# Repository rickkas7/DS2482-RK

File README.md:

# DS2482 Library

The DS2482 is an I2C to 1-wire interface chip. It comes in two versions, the DS2482-100 (1-port) and DS2482-800 (8-port). Using an interface chip is helpful because most DS18B20/1-wire libraries use timing sensitive code and may run for extended periods with interrupts disabled. This can cause the rest of your program to have poor performance. 

The library fully supports both single-drop and multi-drop modes, allowing many DS18B20 sensors on a single 1-wire bus.

The DS2482 library is completely asynchronous, never blocking for more than the time to do an I2C read or write. Interrupts are never disabled.

Every call uses a C++11 lambda completion handler. The second part of this document has a bit of explanation of why and how it works.

The DS2482 also has an internal transistor to pull the 1-wire bus high during temperature conversion and flash writes. This allows the use of parasitic power mode, requiring only two wires for sensors (DQ and GND), with no separate power line. The library supports this as well.

The full API documentation can be browsed at [http://rickkas7.github.io/DS2482-RK/](http://rickkas7.github.io/DS2482-RK/). The same HTML documentation is in the docs folder in Github.

The official Github is: [https://github.com/rickkas7/DS2482-RK](https://github.com/rickkas7/DS2482-RK).

It's in the Particle community libraries as DS2482-RK.

## Common tasks

### Get temperature of one sensor (single-drop)

The code is also in examples, in the 01-single-drop directory.

```
#include "DS2482.h"

SerialLogHandler logHandler;

DS2482 ds(Wire, 3);

const unsigned long CHECK_PERIOD = 30000;
unsigned long lastCheck = 5000 - CHECK_PERIOD;

void setup() {
	Serial.begin(9600);
	ds.setup();

	DS2482DeviceReset::run(ds,  {
		Serial.printlnf("deviceReset=%d", status);
	});

	Serial.println("setup complete");
}

void loop() {

	ds.loop();

	if (millis() - lastCheck >= CHECK_PERIOD) {
		lastCheck = millis();

		// For single-drop you can pass an empty address to get the temperature of the only
		// sensor on the 1-wire bus
		DS24821WireAddress addr;

		DS2482GetTemperatureCommand::run(ds, addr,  {
			if (status == DS2482Command::RESULT_DONE) {
				char buf[32];
				snprintf(buf, sizeof(buf), "%.4f", tempC);

				Serial.printlnf("temperature=%s deg C", buf);
				Particle.publish("temperature", buf, PRIVATE);
			}
			else {
				Serial.printlnf("DS2482GetTemperatureCommand failed status=%d", status);
			}
		});
	}
}
```

### Get temperatures of multiple sensors (multi-drop)

The code is also in examples, in the 02-multi-drop directory.

```
#include "DS2482.h"

SerialLogHandler logHandler;

DS2482 ds(Wire, 3);

DS2482DeviceListStatic<10> deviceList;
const unsigned long CHECK_PERIOD = 30000;
unsigned long lastCheck = 10000 - CHECK_PERIOD;

void setup() {
	Serial.begin(9600);
	ds.setup();

	DS2482DeviceReset::run(ds,  {
		Serial.printlnf("deviceReset=%d", status);
		DS2482SearchBusCommand::run(ds, deviceList,  {

			if (status != DS2482Command::RESULT_DONE) {
				Serial.printlnf("DS2482SearchBusCommand status=%d", status);
				return;
			}

			Serial.printlnf("Found %u devices", deviceList.getDeviceCount());
		});
	});

	Serial.println("setup complete");
}

void loop() {

	ds.loop();

	if (millis() - lastCheck >= CHECK_PERIOD) {
		lastCheck = millis();

		if (deviceList.getDeviceCount() > 0) {

			DS2482GetTemperatureForListCommand::run(ds, deviceList,  {
				if (status != DS2482Command::RESULT_DONE) {
					Serial.printlnf("DS2482GetTemperatureForListCommand status=%d", status);
					return;
				}

				Serial.printlnf("got temperatures!");

				for(size_t ii = 0; ii < deviceList.getDeviceCount(); ii++) {
					Serial.printlnf("%s valid=%d C=%f F=%f",
							deviceList.getAddressByIndex(ii).toString().c_str(),
							deviceList.getDeviceByIndex(ii).getValid(),
							deviceList.getDeviceByIndex(ii).getTemperatureC(),
							deviceList.getDeviceByIndex(ii).getTemperatureF());
				}

			});
		}
		else {
			Serial.printlnf("no devices found");
		}
	}
}
```

### Multi-drop with parasitic power

Just as the previous example, except within loop the call to D2482GetTemperatureListCommand::run has an extra optional fluent parameter, `.withParasiticPower()`.

```
			DS2482GetTemperatureForListCommand::run(ds, deviceList,  {
				if (status != DS2482Command::RESULT_DONE) {
					Serial.printlnf("DS2482GetTemperatureForListCommand status=%d", status);
					return;
				}

				Serial.printlnf("got temperatures!");

				for(size_t ii = 0; ii < deviceList.getDeviceCount(); ii++) {
					Serial.printlnf("%s valid=%d C=%f F=%f",
							deviceList.getAddressByIndex(ii).toString().c_str(),
							deviceList.getDeviceByIndex(ii).getValid(),
							deviceList.getDeviceByIndex(ii).getTemperatureC(),
							deviceList.getDeviceByIndex(ii).getTemperatureF());
				}

			}).withParasiticPower();
```

### Multi-drop with JSON publish

This example is like the previous, except it publishes multiple sensor values via a single Particle.publish in JSON format (up to 10 DS18B20s supported).

The full examples is only in github, in the test-projects/10-multidrop-json directory. This is because it requires another library, JsonParserGeneratorRK, in addition to DS2482-RK.

```
#include "DS2482.h"
#include "JsonParserGeneratorRK.h"

SerialLogHandler logHandler;

DS2482 ds(Wire, 3);

DS2482DeviceListStatic<10> deviceList;
JsonWriterStatic<256> jsonWriter;

const unsigned long CHECK_PERIOD = 30000;
unsigned long lastCheck = 10000 - CHECK_PERIOD;

void setup() {
	Serial.begin(9600);
	ds.setup();

	DS2482DeviceReset::run(ds,  {
		Serial.printlnf("deviceReset=%d", status);
		DS2482SearchBusCommand::run(ds, deviceList,  {

			if (status != DS2482Command::RESULT_DONE) {
				Serial.printlnf("DS2482SearchBusCommand status=%d", status);
				return;
			}

			Serial.printlnf("Found %u devices", deviceList.getDeviceCount());
		});
	});

	Serial.println("setup complete");
}

void loop() {

	ds.loop();

	if (millis() - lastCheck >= CHECK_PERIOD) {
		lastCheck = millis();

		if (deviceList.getDeviceCount() > 0) {

			DS2482GetTemperatureForListCommand::run(ds, deviceList,  {
				if (status != DS2482Command::RESULT_DONE) {
					Serial.printlnf("DS2482GetTemperatureForListCommand status=%d", status);
					return;
				}

				Serial.printlnf("got temperatures!");

				// Initialize the JsonWriter object and sets it to send 2 decimal places
				jsonWriter.init();
				jsonWriter.setFloatPlaces(2);

				// startObject is for the outer object and must be balanced with finishObjectOrArray.
				jsonWriter.startObject();

				// Write the actual temperatures
				for(size_t ii = 0; ii < deviceList.getDeviceCount(); ii++) {
					if (deviceList.getDeviceByIndex(ii).getValid()) {
						// This creates a key of the form "t0" for the first, "t1" for the second, ...
						char key[4];
						key[0] = 't';
						key[1] = '0' + ii;
						key[2] = 0;

						// Inserts the float as a key value pair
						jsonWriter.insertKeyValue(key, deviceList.getDeviceByIndex(ii).getTemperatureC());
					}
				}

				jsonWriter.finishObjectOrArray();

				Serial.println(jsonWriter.getBuffer());
				Particle.publish("temperature", jsonWriter.getBuffer(), PRIVATE);

				// Example output:
				// {"t0":23.56,"t1":23.12}
			});
		}
		else {
			Serial.printlnf("no devices found");
		}
	}
}
```

Example serial output:

```
got temperatures!
{"t0":23.56,"t1":23.12}
```

Because the 1-wire bus search is deterministic, it will always returns the sensors in the same order, sorted by 1-wire device address (increasing).

### Test Suite

There's a test suite for the library in Github, in test-projects/11-testboard. This is a hardware and software combination used to do regression testing on the library.

## About lambdas, fluent-style and more

The DS2482 library uses a C++11 style of coding that is very powerful, but will probably be foreign to you if you learned old-school C and C++. It's actually more like the way Javascript/node.js is programmed.

One of the main advantages of the DS2482 library is that it's completely asynchronous. No call blocks for more than the time it takes to make an I2C transfer. This is important because getting a temperature sensor reading can take 750 milliseconds, and most DS18B20 software libraries block during conversion.

### Synchronous way

Using the [DS18B20 library](https://build.particle.io/libs/DS18B20/0.1.7/tab/DS18B20.cpp), you make a call like this:

```
float tempC = ds.getTemperature(addr);
```

The main loop thread is blocked during this call for 750 milliseconds, which may affect performance elsewhere in your code. 

### State machines

One common way of implementing asynchronous code is state machines. This is a bit of pseudo-code of what a state machine version might look like. 

```
void loop() {
	switch(state) {
	case GET_TEMPERATURE_STATE:
		ds.startTemperature();
		state = TEMPERATURE_WAIT_STATE;
		break;

	case TEMPERATURE_WAIT_STATE:
		if (ds.isTemperatureDone()) {
			float temp = ds.readTemperature();
			state = ANOTHER_STATE;
		}
		break;
	}
}
```

State machines are really powerful, and actually how the DS2482 library is implemented internally, but can get a bit unwieldy.

### Callbacks

Callback functions are another common way of handling asynchronous code, like in this pseudo-code example:

```
void temperatureCallback(float temp) {
	Serial.printlnf("got temperature %f", temp);
}

void loop() {
	if (millis() - lastCheck >= CHECK_PERIOD) {
		lastCheck = millis();
		ds.getTemperature(temperatureCallback);
	}
}
```

The problem with callbacks is that it's a pain to pass state data to the callback, and it requires some effort to make a callback handler a class member function.

### The Lambda

The lambda solves some of the problems with callbacks. Here's an example of doing an asynchronous device reset call:

```
void setup() {
	Serial.begin(9600);
	ds.setup();

	DS2482DeviceReset::run(ds,  {
		Serial.printlnf("deviceReset=%d", status);
	});

	Serial.println("setup complete");
}
```

The syntax is a little weird, and I'll get to that a moment, however the important thing is that this block of code, the lambda, is executed later.

```
	 {
		Serial.printlnf("deviceReset=%d", status);
	}
```

The 

```
setup complete
```

message appears next.

When the asynchronous device reset completes, the block runs and

```
deviceReset=1
``` 

will likely be printed to the serial console. Note, however, that the lines after the block, like printing setup complete! won't happen a second time.

A declaration of a lambda function looks like 

```
 {
	// Code goes here
}
``` 

The `[]` part is the capture, which we'll discuss in a moment, and `(DS2482DeviceReset&, int status)` is a function parameter declaration. Basically the callback is a function that takes two parameters, a `DS2482DeviceReset&` object (not used here) and an `int status` (for status).

### Nesting calls

This example demonstrates two handy things:

- Making your lambda be a class member
- Nesting lambdas for sequential operations

```
void TestClass::check() {
	DS2482SearchBusCommand::run(ds, deviceList, [this](DS2482SearchBusCommand &obj, int status) {

		if (status != DS2482Command::RESULT_DONE) {
			Serial.printlnf("DS2482SearchBusCommand status=%d", status);
			return;
		}

		if (deviceList.getDeviceCount() == 0) {
			Serial.println("no devices");
			return;
		}

		DS2482GetTemperatureForListCommand::run(ds, obj.getDeviceList(), [this](DS2482GetTemperatureForListCommand&, int status, DS2482DeviceList &deviceList) {
			if (status != DS2482Command::RESULT_DONE) {
				Serial.printlnf("DS2482GetTemperatureForListCommand status=%d", status);
				return;
			}

			Serial.printlnf("got temperatures!");

			for(size_t ii = 0; ii < deviceList.getDeviceCount(); ii++) {
				Serial.printlnf("%s valid=%d C=%f F=%f",
						deviceList.getAddressByIndex(ii).toString().c_str(),
						deviceList.getDeviceByIndex(ii).getValid(),
						deviceList.getDeviceByIndex(ii).getTemperatureC(),
						deviceList.getDeviceByIndex(ii).getTemperatureF());
			}

		});
	});
}
```

You'll notice the slightly different syntax in the capture, the part in the square brackets:

```
DS2482SearchBusCommand::run(ds, deviceList, [this](DS2482SearchBusCommand &obj, int status) {
```

Instead of just being `[]` it's `[this]`. That means that `this`, your class instance, is captured, and available inside the lambda. It essentially makes the inner function a class member, available to access class member functions and variables.

You can capture multiple variables, separated by commas. You can capture function parameters and local variables, for example.

The other thing is that you can nest these, so each new indent in occurs at a later time. If you don't like that style, however, you can just split your code into separate member functions like this:

```
void TestClass::searchBus() {

	DS2482SearchBusCommand::run(ds, deviceList, [this](DS2482SearchBusCommand &obj, int status) {

		if (status != DS2482Command::RESULT_DONE) {
			Serial.printlnf("DS2482SearchBusCommand status=%d", status);
			return;
		}

		if (deviceList.getDeviceCount() == 0) {
			Serial.println("no devices");
			return;
		}

		getTemperatures();
	});
}

void TestClass::getTemperatures() {

	DS2482GetTemperatureForListCommand::run(ds, deviceList, [this](DS2482GetTemperatureForListCommand&, int status, DS2482DeviceList &deviceList) {
		if (status != DS2482Command::RESULT_DONE) {
			Serial.printlnf("DS2482GetTemperatureForListCommand status=%d", status);
			return;
		}

		Serial.printlnf("got temperatures!");

		for(size_t ii = 0; ii < deviceList.getDeviceCount(); ii++) {
			Serial.printlnf("%s valid=%d C=%f F=%f",
					deviceList.getAddressByIndex(ii).toString().c_str(),
					deviceList.getDeviceByIndex(ii).getValid(),
					deviceList.getDeviceByIndex(ii).getTemperatureC(),
					deviceList.getDeviceByIndex(ii).getTemperatureF());
		}
	});

}
```

### Optional parameters

Within the library, optional parameters are passed fluent-style instead of using C++ optional parameters. The fluent-style parameters are easier to identify and don't depend on order. For example:

```
DS2482GetTemperatureCommand::run(ds, addr, [this,completion](DS2482GetTemperatureCommand&, int status, float t) {
		if (status != DS2482Command::RESULT_DONE) {
			Log.error("FAILURE DS2482GetTemperatureCommand failed %d bus %s", status, name.c_str());
			completion();
			return;
		}

		testsComplete(completion);
	}).withParasiticPower(isParasiticPowered).withMaxRetries(1);
```

Of note:

- The optional parameters go after the `})` that closes the run command.
- You can chain as many or as few as you want in any order.
- The names all begin with `with`.

In this example, it uses parasitic power or not based on the member variable `isParasiticPowered` and limits the number of retries to 1.

### Run methods

All of the asynchronous functions are implemented as separate classes with a static run method. For example `DS2482GetTemperatureCommand::run`.

This is done because the objects need to be allocated on the heap (using new), not stack allocated. Since they continue after your function returns, stack allocated classes wouldn't work because they would go away when the enclosing function returns.

The run methods take care of allocated the objects and enqueueing them for execution so they make sure the objects gets deleted later, as well.

## Hardware examples

The hardware examples are in Github in the hardware directory. The Eagle board and schematic files are there as well.

### 1-port

This is a simple breakout board for the DS2482-100 (1-port):

### 8-port

This is a simple board for the DS2482-800 (8-port), though it's only populated for 6 ports. Four of them are modular jacks, designed to connect with one of the remote sensors below.

### DS18B20-regular

This is a simple DS18B20 remote sensor with a modular connector. The extra chip is a bridge rectifier, which makes it tolerant of having the connector polarity reversed, for example yellow and black reversed. This happens frequently when the flat cable is used and there isn't the proper twist in it.

### DS18B20-Mini

This is an even smaller DS18B20 remote sensor with a modular connector. It leaves off the screw terminal space and does not include the bridge rectifier, so make sure you don't cross the yellow and black wires!

### test-board

This is how I regression test the library. It's a board with DS2482-100 (1-port), DS2482-800 (8-port), 8x DS18B20s, and MCP23008 so I can switch the DS18B20s between powered and parasitic power mode individually.

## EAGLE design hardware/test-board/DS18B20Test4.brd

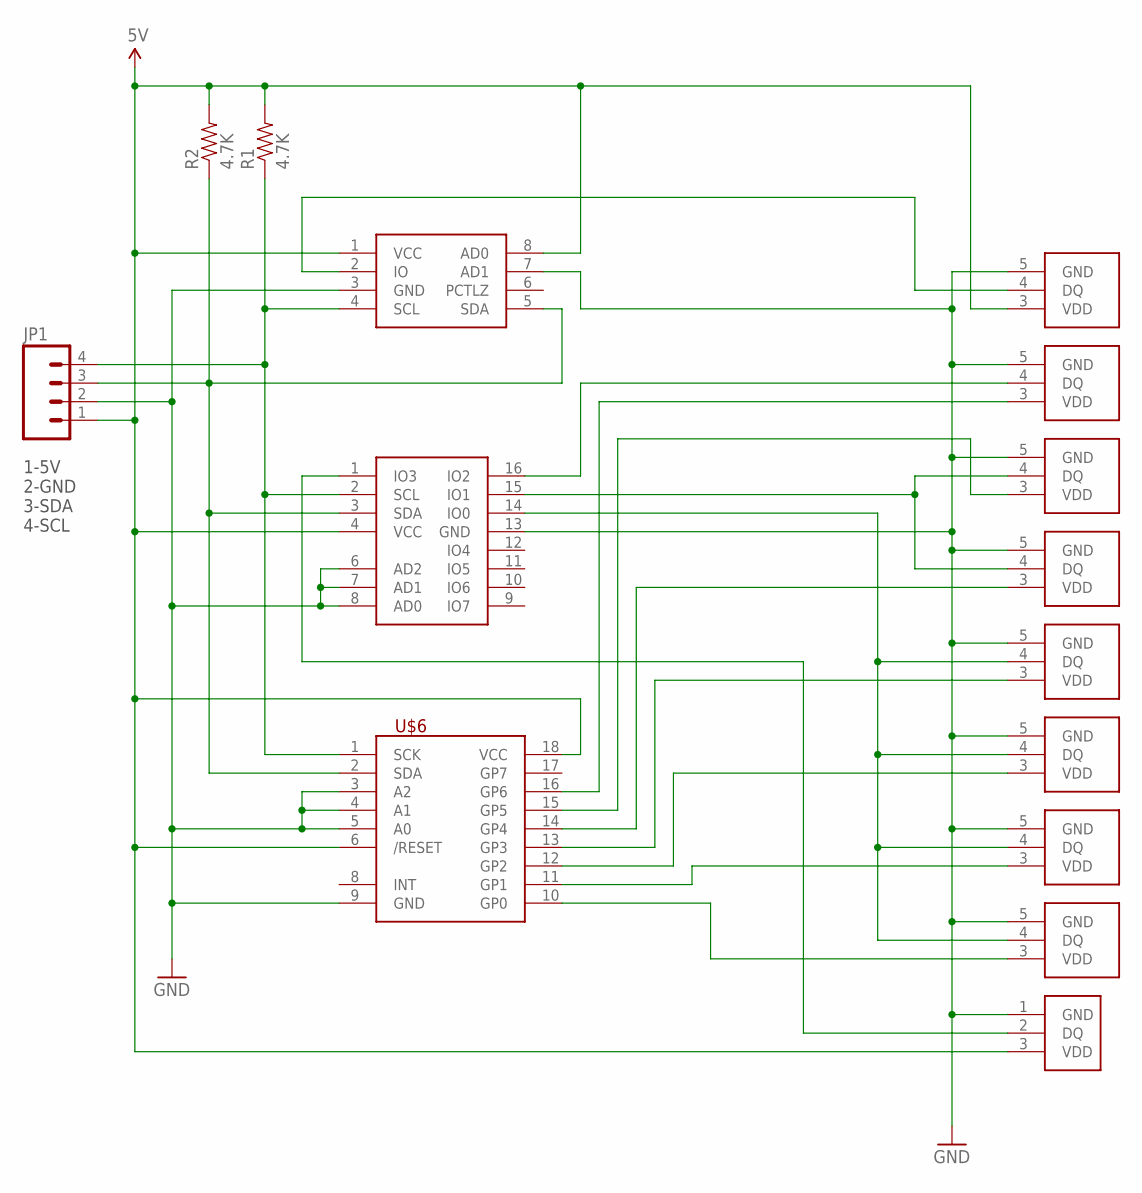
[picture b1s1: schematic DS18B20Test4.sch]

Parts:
JP1: M04PTH; 1X04
R1, R2: 4.7K; 0603-RES
U$1: DS2482-100; 8-SOIC-MAXIM
U$2: DS2482-800; 16-SOIC-MAXIM
U$3: TERMBLOCK-1WIRE
U$4, U$5, U$7, U$8, U$9, U$10, U$11, U$12: DS18B208-SOIC; DS18B20-S0
U$6: MCP23008; SOIC-18-W-MAXIM

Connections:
5V: JP1.1, R1.2, R2.2, U$1.1 (VCC), U$1.8 (AD0), U$2.4 (VCC), U$3.3 (VDD), U$4.3 (VDD), U$6.6 (/RESET), U$6.18 (VCC)
GND: JP1.2, U$1.3 (GND), U$1.7 (AD1), U$2.6 (AD2), U$2.7 (AD1), U$2.8 (AD0), U$2.13 (GND), U$3.1 (GND), U$4.5 (GND), U$5.5 (GND), U$6.3 (A2), U$6.4 (A1), U$6.5 (A0), U$6.9 (GND), U$7.5 (GND), U$8.5 (GND), U$9.5 (GND), U$10.5 (GND), U$11.5 (GND), U$12.5 (GND)
unnamed: U$1.2 (IO), U$4.4 (DQ)
unnamed: U$2.16 (IO2), U$5.4 (DQ)
unnamed: U$2.15 (IO1), U$7.4 (DQ), U$8.4 (DQ)
unnamed: U$2.14 (IO0), U$9.4 (DQ), U$10.4 (DQ), U$11.4 (DQ), U$12.4 (DQ)
unnamed: U$2.1 (IO3), U$3.2 (DQ)
unnamed: U$5.3 (VDD), U$6.16 (GP6)
unnamed: U$6.15 (GP5), U$7.3 (VDD)
unnamed: U$6.14 (GP4), U$8.3 (VDD)
unnamed: U$6.13 (GP3), U$9.3 (VDD)
unnamed: U$6.12 (GP2), U$10.3 (VDD)
unnamed: U$6.11 (GP1), U$11.3 (VDD)
unnamed: U$6.10 (GP0), U$12.3 (VDD)
SCL: JP1.4, R1.1, U$1.4 (SCL), U$2.2 (SCL), U$6.1 (SCK)
SDA: JP1.3, R2.1, U$1.5 (SDA), U$2.3 (SDA), U$6.2 (SDA)

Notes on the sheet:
1-5V 2-GND 3-SDA 4-SCL

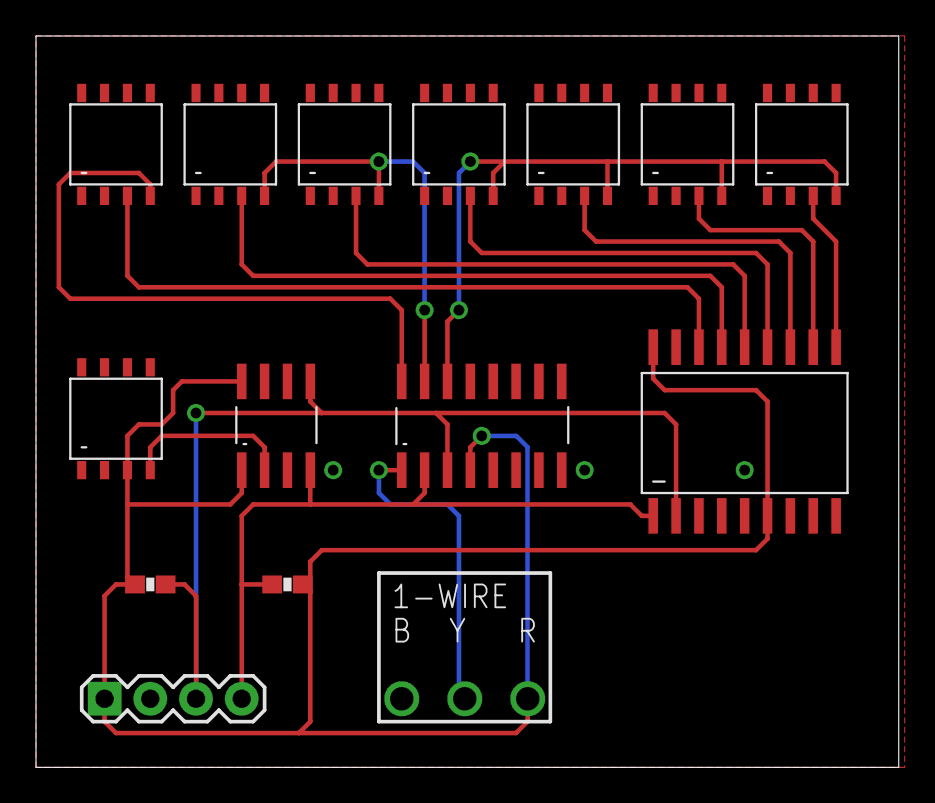
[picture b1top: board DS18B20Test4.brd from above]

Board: 2 copper layers, 47.9 x 40.6 mm, 15 parts (0 on the bottom side), 16 nets.

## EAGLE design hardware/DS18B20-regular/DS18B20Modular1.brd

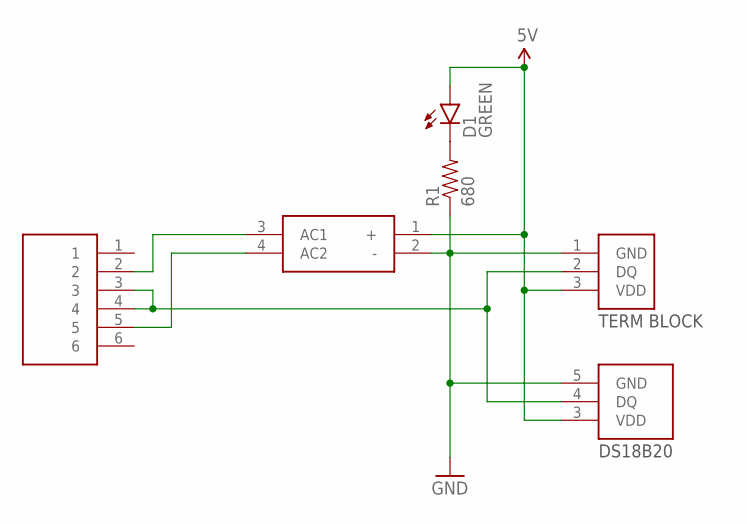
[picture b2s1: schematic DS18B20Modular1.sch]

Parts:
D1: GREEN; LED-0603
J1: MODULAR-JACK-6P6C-1
R1: 680; 0805
U$1: RECTIFIER-MB1S; 4-SOIC-FAIRCHILD
U$2: TERMBLOCK-1WIRE
U$3: DS18B208-SOIC; DS18B20-S0

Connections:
5V: D1.A, U$1.1 (+), U$2.3 (VDD), U$3.3 (VDD)
GND: R1.1, U$1.2 (-), U$2.1 (GND), U$3.5 (GND)
unnamed: J1.3, J1.4, U$2.2 (DQ), U$3.4 (DQ)
unnamed: J1.2, U$1.3 (AC1)
unnamed: J1.5, U$1.4 (AC2)
unnamed: D1.C, R1.2

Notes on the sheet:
DS18B20
TERM BLOCK

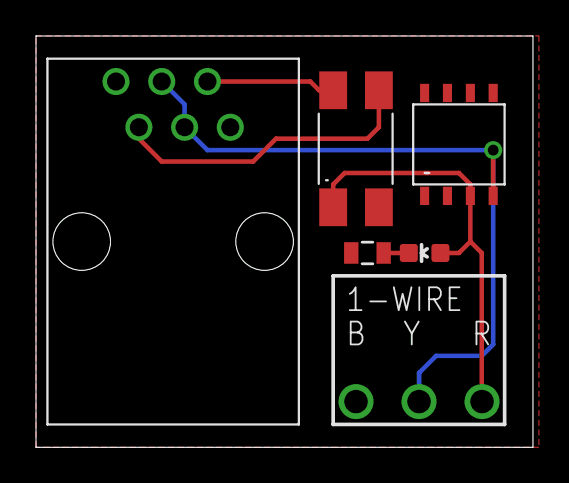
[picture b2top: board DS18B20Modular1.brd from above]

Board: 2 copper layers, 27.6 x 22.9 mm, 6 parts (0 on the bottom side), 6 nets.

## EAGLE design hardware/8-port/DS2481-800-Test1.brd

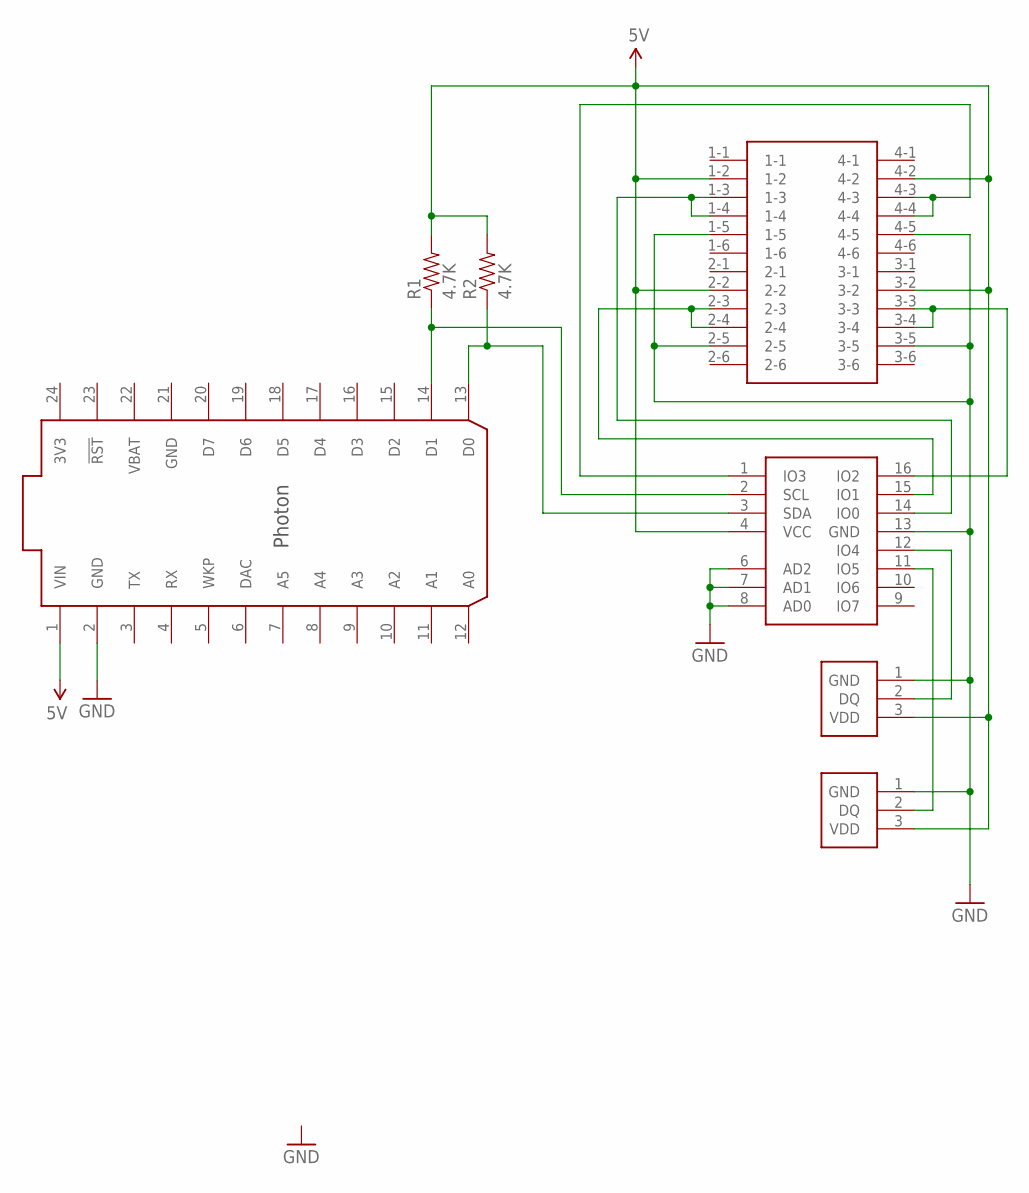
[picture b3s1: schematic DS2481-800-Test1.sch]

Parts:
R1, R2: 4.7K; 0603-RES
U$1: PHOTON_WITH_HEADERS; PHOTON
U$2: DS2482-800; 16-SOIC-MAXIM
U$3: MODULAR-JACK-6P6C-4
U$4, U$5: TERMBLOCK-1WIRE

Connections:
3V3: U$1.24 (3V3)
5V: R1.2, R2.2, U$1.1 (VIN), U$2.4 (VCC), U$3.1-2, U$3.2-2, U$3.3-2, U$3.4-2, U$4.3 (VDD), U$5.3 (VDD)
GND: U$1.2 (GND), U$1.21 (GND), U$2.6 (AD2), U$2.7 (AD1), U$2.8 (AD0), U$2.13 (GND), U$3.1-5, U$3.2-5, U$3.3-5, U$3.4-5, U$4.1 (GND), U$5.1 (GND)
unnamed: U$2.14 (IO0), U$3.1-3, U$3.1-4
unnamed: U$2.15 (IO1), U$3.2-3, U$3.2-4
unnamed: U$2.16 (IO2), U$3.3-3, U$3.3-4
unnamed: U$2.1 (IO3), U$3.4-3, U$3.4-4
unnamed: U$2.12 (IO4), U$4.2 (DQ)
unnamed: U$2.11 (IO5), U$5.2 (DQ)
unnamed: R2.1, U$1.13 (D0), U$2.3 (SDA)
unnamed: R1.1, U$1.14 (D1), U$2.2 (SCL)
VBAT: U$1.22 (VBAT)

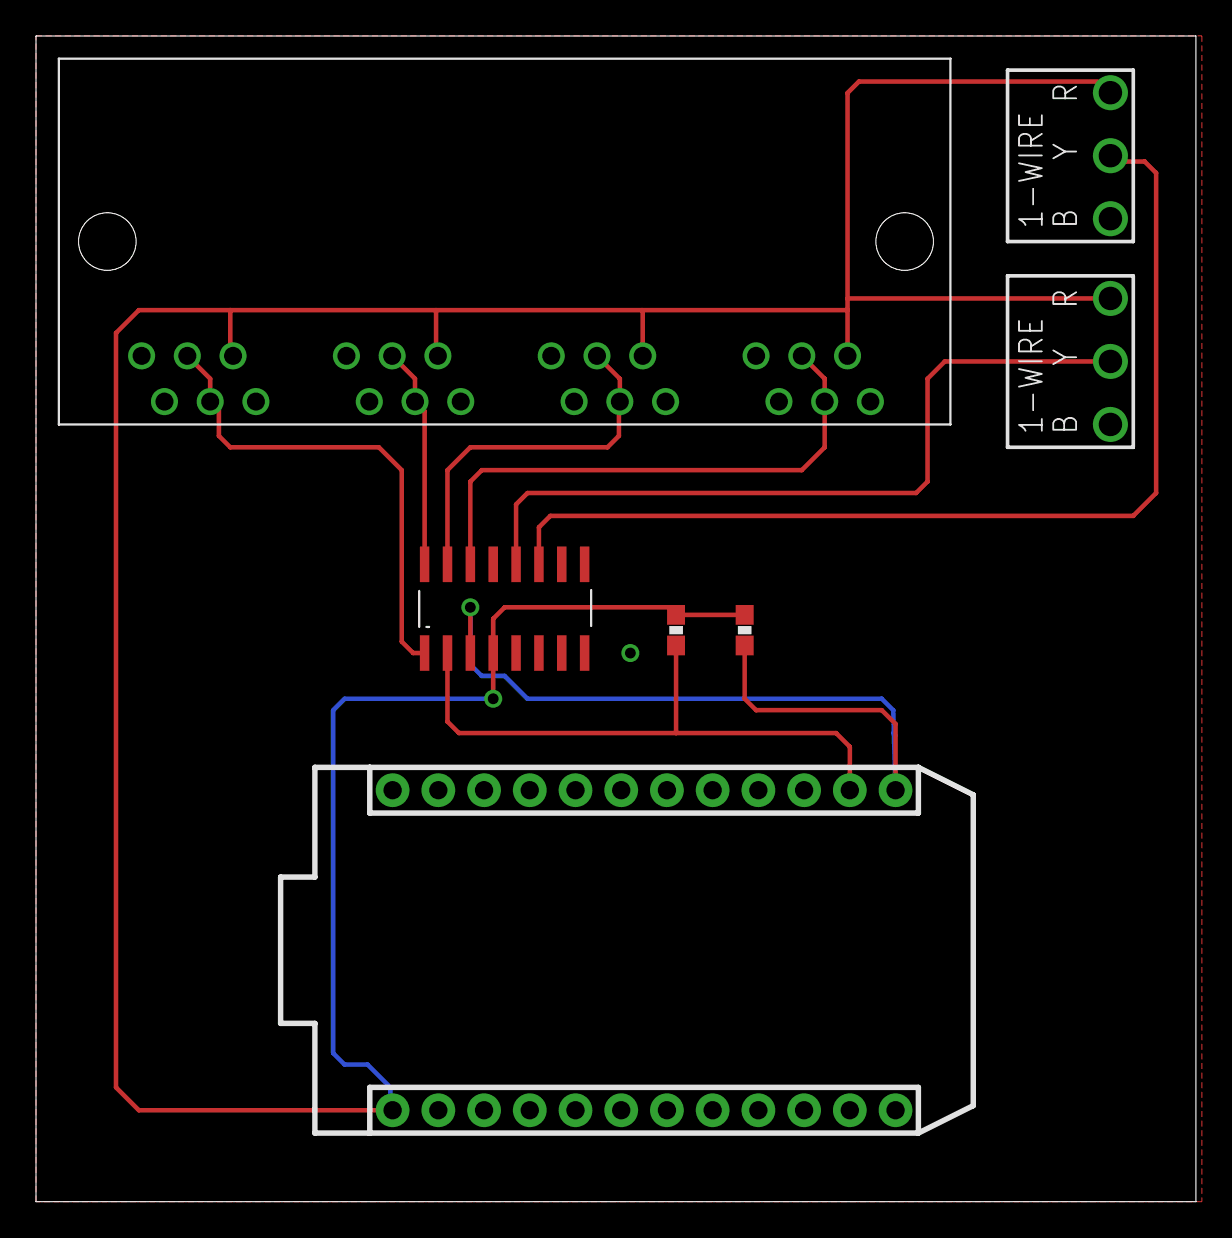
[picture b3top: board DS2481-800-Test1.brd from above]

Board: 2 copper layers, 64.4 x 64.8 mm, 7 parts (0 on the bottom side), 10 nets.

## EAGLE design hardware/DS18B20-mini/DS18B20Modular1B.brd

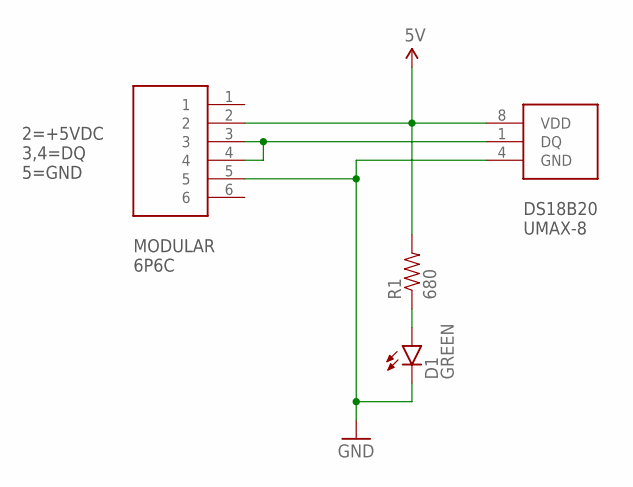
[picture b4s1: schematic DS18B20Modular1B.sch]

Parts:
D1: GREEN; LED-0603
J1: MODULAR-JACK-6P6C-1
R1: 680; 0805
U$1: DS18B20UMAX-8; UMAX-8-MAXIM

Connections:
5V: J1.2, R1.2, U$1.8 (VDD)
GND: D1.C, J1.5, U$1.4 (GND)
unnamed: D1.A, R1.1
unnamed: J1.3, J1.4, U$1.1 (DQ)

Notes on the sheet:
2=+5VDC 3,4=DQ 5=GND
DS18B20 UMAX-8
MODULAR 6P6C

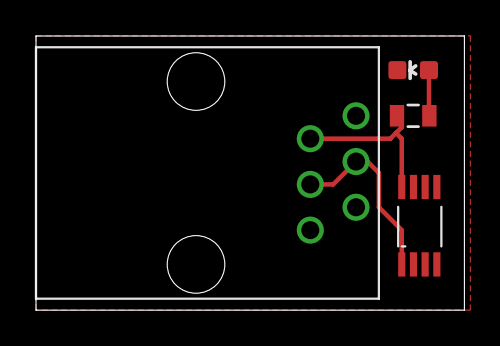
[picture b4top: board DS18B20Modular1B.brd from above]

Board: 2 copper layers, 23.8 x 15.2 mm, 4 parts (0 on the bottom side), 4 nets.

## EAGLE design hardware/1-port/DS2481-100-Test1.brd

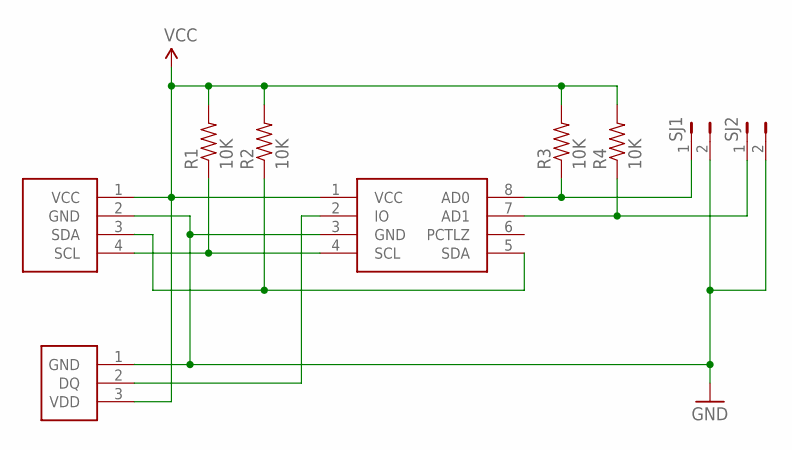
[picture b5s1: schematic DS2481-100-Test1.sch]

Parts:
R1, R2, R3, R4: 10K; 0603-RES
SJ1, SJ2: JUMPER-PTH-2-NO; PTH-JUMPER-2-NO_NO_SILK
U$1: HEADER-I2C-PWR
U$2: DS2482-100; 8-SOIC-MAXIM
U$3: TERMBLOCK-1WIRE

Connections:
GND: SJ1.2, SJ2.2, U$1.2 (GND), U$2.3 (GND), U$3.1 (GND)
unnamed: U$2.2 (IO), U$3.2 (DQ)
unnamed: R1.1, U$1.4 (SCL), U$2.4 (SCL)
unnamed: R2.1, U$1.3 (SDA), U$2.5 (SDA)
unnamed: R3.1, SJ1.1, U$2.8 (AD0)
unnamed: R4.1, SJ2.1, U$2.7 (AD1)
VCC: R1.2, R2.2, R3.2, R4.2, U$1.1 (VCC), U$2.1 (VCC), U$3.3 (VDD)

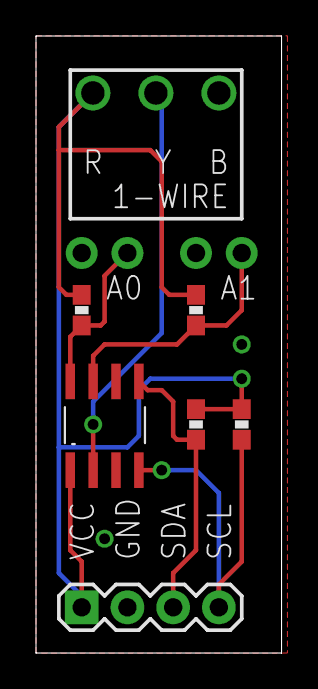
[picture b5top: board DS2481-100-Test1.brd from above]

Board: 2 copper layers, 13.6 x 34.3 mm, 9 parts (0 on the bottom side), 7 nets.

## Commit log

2018-03-17 version 0.0.2
2018-07-03 travis test
2018-07-03 travis test 2
2018-07-03 more travis tests
2019-01-24 Version 0.0.3
    Change example address default to 0
    Add travis builds for mesh devices
